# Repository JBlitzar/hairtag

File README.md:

# hairtag

homemade airtag that's genuinely pretty good

 - ESP32C3 chip, openhaystack firmware (more FOSS than Apple, no crazy custom die)
 - 22mm diameter board (smaller than Apple's 33, although technically the product is taller overall)
 - Probably costs less than Apple (legit like $2 per board after paying the $40 flat setup fees)
    - (but if cost was really what you were hoping for, buy an aliexpress knockoff)
 - Comparable battery life to apple! (~229 days theoretically)
    - Actually configurable depending on what temporal accuracy you need and which ma consumption figure you believe: https://www.desmos.com/calculator/mcncridlhq
 - Designed in California (just like apple lol)

 ## Why I made this project

 I thought airtags were pretty cool. A while ago I was scrolling Github and I came across [openhaystack](https://github.com/seemoo-lab/openhaystack) (btw Seemoo lab has done all sorts of cool things that I've used before, shoutout to nexmon and opendrop). 

 Anyways, I figured I could make my own. It's good experience, because you basically get all the components of a devboard, plus power budgeting, and interesting firmware. Plus, I already own 10000 devboards but I own zero airtags so this is a product that I'd actually use and want. A project that has both cool value and educational value gives you so much more motivation than one that only has the latter. 

## Schematic

## PCB

## Wiring diagram for flashing

The standard way is a CP2102 USB-UART dongle wired straight to the flashing header (VCC, GND, TXD, RXD, EN, DTR):

Alternatively, if you have an [Icepi Zero](https://www.crowdsupply.com/icy-electronics/icepi-zero) FPGA, you can use its onboard USB-UART bridge as the flasher. See [`software/fpga/`](software/fpga/).

## Gallery

https://github.com/user-attachments/assets/a9827342-8f9d-4dc0-8821-d6cf14613d8d

## Usage instructions

See [`software/README.md`](software/README.md). It's quite involved.

## Bom

|Item                     |Link                                                                     |Cost |Notes                                                                                                                       |Running Total|
|-------------------------|-------------------------------------------------------------------------|-----|----------------------------------------------------------------------------------------------------------------------------|-------------|
|CP2102 for flashing      |http://waveshare.com/cp2102-usb-uart-board-type-a.htm                    |4.99 |This one has a specific pinout that's useful, also waveshare's more reputable                                               |4.99         |
|PCB + PCBA + JLC shipping|N/A                                                                      |42.02|Cost for 2x pcba. I'm willing to pay $4 extra out of pocket to get the 5x PCBA                                              |47.01        |
|CR2032 batteries         |https://www.aliexpress.us/item/3256808176964698.html                     |0    |self-sourced, alt amazon link: https://www.amazon.com/Energizer-2032-Battery-CR2032-Lithium/dp/B0042A9UXC?th=1              |47.01        |
|battery holder           |https://www.amazon.com/RuiLing-CR2032-Button-Battery-Holder/dp/B07PNK5D6H|6.69 |it's actually cheaper than what I could find on aliexpress (at least that had the footprint that I wanted and free shipping)|53.7         |
|Shipping / taxes         |N/A                                                                      |11   |TBD, from all the other ones not counting pcba                                                                              |64.7         |
|Case (printed)           |N/A                                                                      |0    |self-sourced, alternatively print legion is also free                                                                                                                |64.7         |

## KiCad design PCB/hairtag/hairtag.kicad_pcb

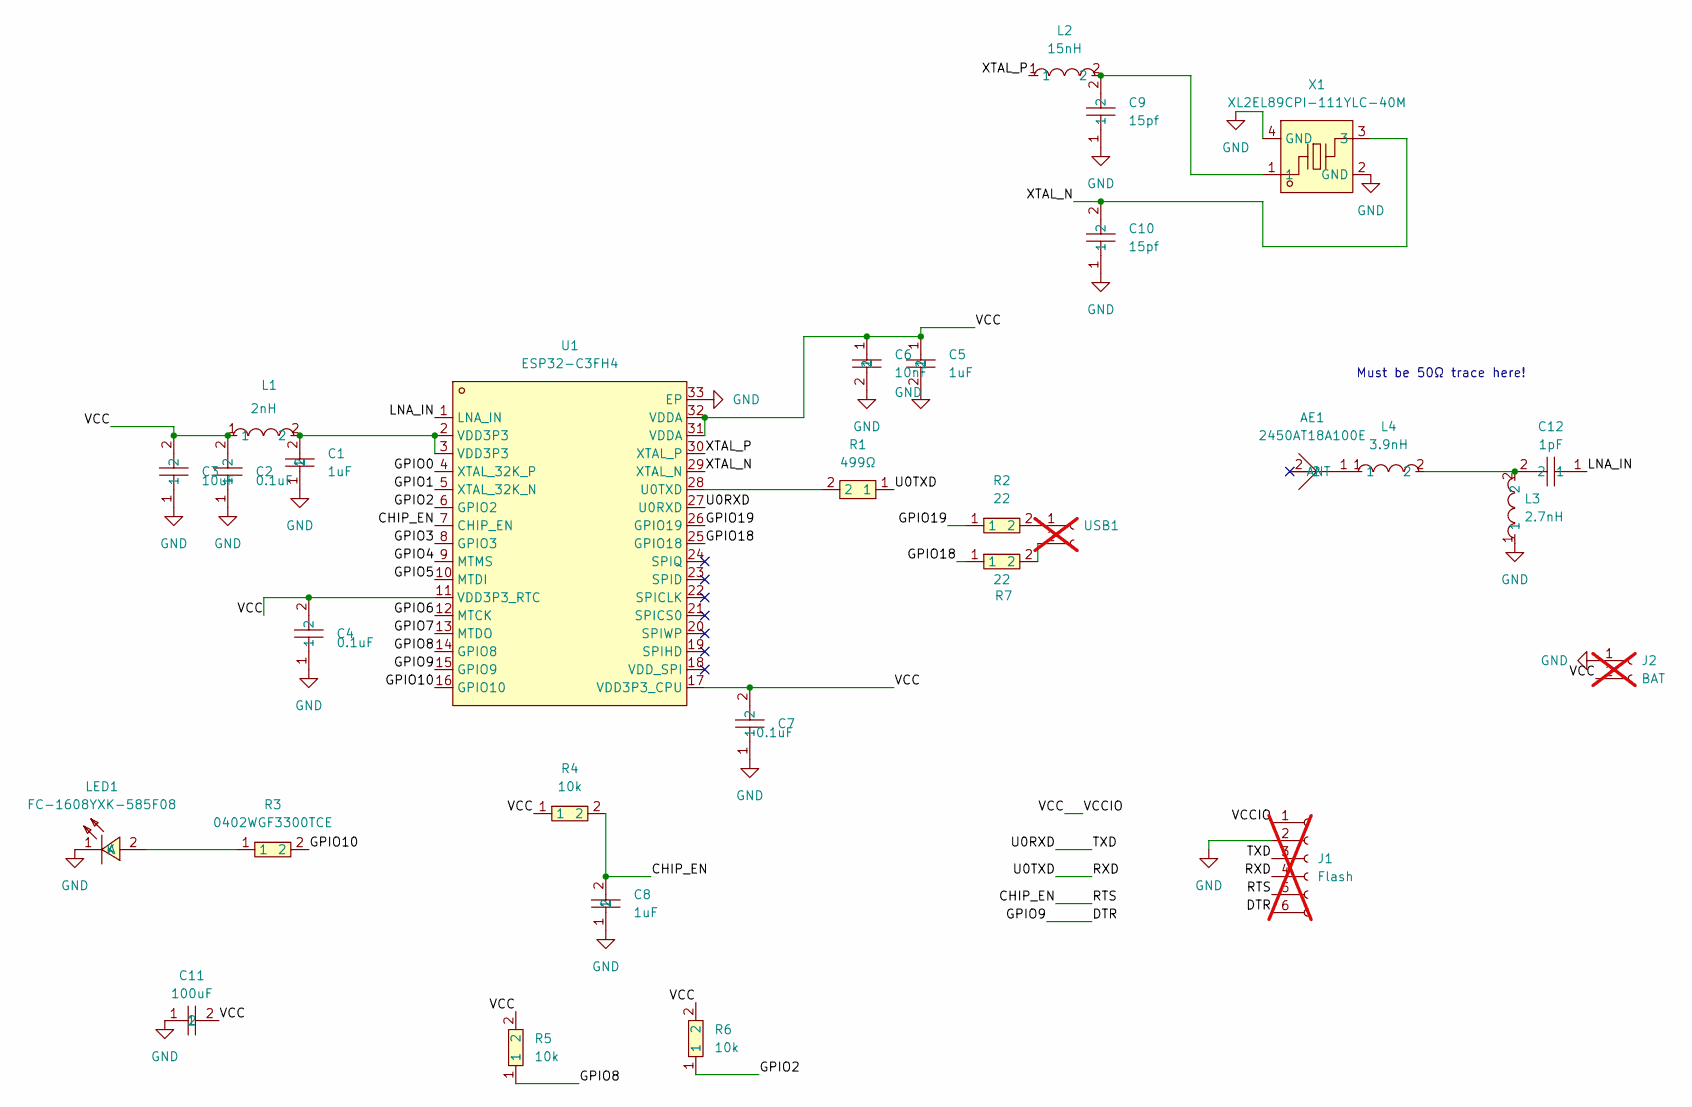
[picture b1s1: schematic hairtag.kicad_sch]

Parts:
AE1: 2450AT18A100E; ANT-SMD_L3.2-W1.6; MPN 2450AT18A100E; LCSC Part C89334
C1, C5, C8: 1uF; C0402; MPN CL05A105KA5NQNC; LCSC Part C52923
C2, C4, C7: 0.1uF; C0402; MPN CL05B104KO5NNNC; LCSC Part C1525
C3: 10uF; C0402; MPN CL05A106MQ5NUNC; LCSC Part C15525
C6: 10nF; C0402; MPN CL05B103KB5NNNC; LCSC Part C15195
C9, C10: 15pf; C0402; MPN 0402CG150J500NT; LCSC Part C1548
C11: 100uF; C1206; MPN CL31A107MQHNNNE; LCSC Part C15008
C12: 1pF; C0402; MPN 0402CG1R0C500NT; LCSC Part C1550
J1: Flash; PinSocket_1x06_P2.54mm_Vertical; not fitted
J2: BAT; Untitled; not fitted
L1: 2nH; L0402; MPN MLG1005S2N0BT000; LCSC Part C76769
L2: 15nH; L0402; MPN SDCL1005C15NJTDF; LCSC Part C27143
L3: 2.7nH; L0402; MPN SDCL1005C2N7STDF; LCSC Part C27123
L4: 3.9nH; IND-SMD_L1.0-W0.5-2; MPN LQW15AN3N9B00D; LCSC Part C98062
LED1: FC-1608YXK-585F08; LED0603-RD; MPN KT-0603R; LCSC Part C2286
R1: 499Ω; R0402; MPN FRC0402F4990TS; LCSC Part C2960788
R2, R7: 22; R0402; MPN 0402WGF220JTCE; LCSC Part C25092
R3: 0402WGF3300TCE; R0402; MPN 0402WGF3300TCE; LCSC Part C25104
R4, R5, R6: 10k; R0402; MPN 0402WGF1002TCE; LCSC Part C25744
U1: ESP32-C3FH4; QFN-32_L5.0-W5.0-P0.50-TL-EP3.7; MPN ESP32-C3FH4; LCSC Part C2858491
USB1: USB; PinSocket_1x02_P2.54mm_Vertical; not fitted
X1: XL2EL89CPI-111YLC-40M; CRYSTAL-SMD_4P-L3.2-W2.5-BL; MPN XL2EL89CPI-111YLC-40M; LCSC Part C5444549

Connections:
/CHIP_EN: C8.2, J1.5, R4.2, U1.7 (CHIP_EN)
/DTR: J1.6, U1.15 (GPIO9)
/GPIO0: U1.4 (XTAL_32K_P)
/GPIO1: U1.5 (XTAL_32K_N)
/GPIO2: R6.1, U1.6 (GPIO2)
/GPIO3: U1.8 (GPIO3)
/GPIO4: U1.9 (MTMS)
/GPIO5: U1.10 (MTDI)
/GPIO6: U1.12 (MTCK)
/GPIO7: U1.13 (MTDO)
/GPIO8: R5.1, U1.14 (GPIO8)
/GPIO10: R3.2, U1.16 (GPIO10)
/GPIO18: R7.1, U1.25 (GPIO18)
/GPIO19: R2.1, U1.26 (GPIO19)
/LNA_IN: C12.1, U1.1 (LNA_IN)
/RXD: J1.4, R1.1
/TXD: J1.3, U1.27 (U0RXD)
/VCC: C2.2, C3.2, C4.2, C5.1, C6.1, C7.2, C11.2, J1.1, J2.2, L1.1, R4.1, R5.2, R6.2, U1.11 (VDD3P3_RTC), U1.17 (VDD3P3_CPU), U1.31 (VDDA), U1.32 (VDDA)
/XTAL_N: C10.2, U1.29 (XTAL_N), X1.3
/XTAL_P: L2.1, U1.30 (XTAL_P)
GND: C1.1, C2.1, C3.1, C4.1, C5.2, C6.2, C7.1, C8.1, C9.1, C10.1, C11.1, J1.2, J2.1, L3.1, LED1.1 (K), U1.33 (EP), X1.2 (GND), X1.4 (GND)
unnamed: AE1.1 (ANT_1), L4.1
unnamed: C1.2, L1.2, U1.2 (VDD3P3), U1.3 (VDD3P3)
unnamed: C9.2, L2.2, X1.1
unnamed: C12.2, L3.2, L4.2
unnamed: LED1.2 (A), R3.1
unnamed: R1.2, U1.28 (U0TXD)
unnamed: R2.2, USB1.1
unnamed: R7.2, USB1.2

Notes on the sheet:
Must be 50Ω trace here!

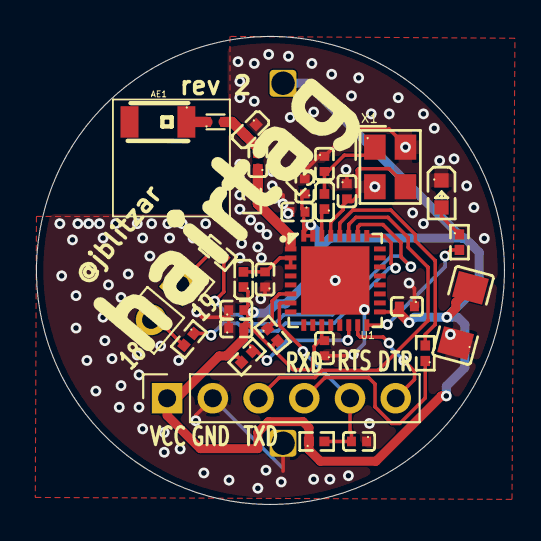
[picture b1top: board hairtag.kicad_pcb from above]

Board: 2 copper layers, 26.0 x 26.0 mm, 30 parts (1 on the bottom side), 22 nets.

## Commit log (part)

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2026-06-05 lwk the schematic
2026-06-05 asdf
2026-06-05 ditch ldo
2026-06-05 cram
2026-06-05 routing
2026-06-06 misc stuff
2026-06-06 readme stuff
2026-06-06 readme
2026-06-06 clean up tracks and vias
2026-06-06 stuff
2026-06-06 3d top
2026-06-06 blend
2026-06-06 better render, going to cook on anim
2026-06-06 video
2026-06-06 updated blend
2026-06-06 note to the reviewers
2026-06-06 firmware!!
2026-06-06 roller coaster of firmware
2026-06-06 thing
2026-06-06 whole assembly
2026-06-06 locate.sh
2026-06-06 prettytable
2026-06-06 swap generic SF with generic ocean
2026-06-07 reformat, use hint byte
2026-06-07 how to flash bare esp
2026-06-07 hint byte
2026-06-07 usage
2026-06-07 rm pycs
2026-06-07 ungitignore csv files
2026-06-07 fix the logic error sob
2026-06-07 resave
2026-06-08 slop
2026-06-10 refill I guess
2026-06-14 Update README.md
    Remove note now that it's approved
2026-06-20 Bump cryptography from 48.0.0 to 48.0.1 in /firmware/findmy
    Bumps [cryptography](https://github.com/pyca/cryptography) from 48.0.0 to 48.0.1.
    - [Changelog](https://github.com/pyca/cryptography/blob/main/CHANGELOG.rst)
    - [Commits](https://github.com/pyca/cryptography/compare/48.0.0...48.0.1)
    ---
    updated-dependencies:
    - dependency-name: cryptography
2026-06-20 Bump cryptography in /firmware/esp32c3-openhaystack
    Bumps [cryptography](https://github.com/pyca/cryptography) from 48.0.0 to 48.0.1.
    - [Changelog](https://github.com/pyca/cryptography/blob/main/CHANGELOG.rst)
    - [Commits](https://github.com/pyca/cryptography/compare/48.0.0...48.0.1)
    ---
    updated-dependencies:
    - dependency-name: cryptography
2026-06-29 add LED
2026-06-29 reorganize
2026-06-29 tweaks
2026-06-29 ordered it!
